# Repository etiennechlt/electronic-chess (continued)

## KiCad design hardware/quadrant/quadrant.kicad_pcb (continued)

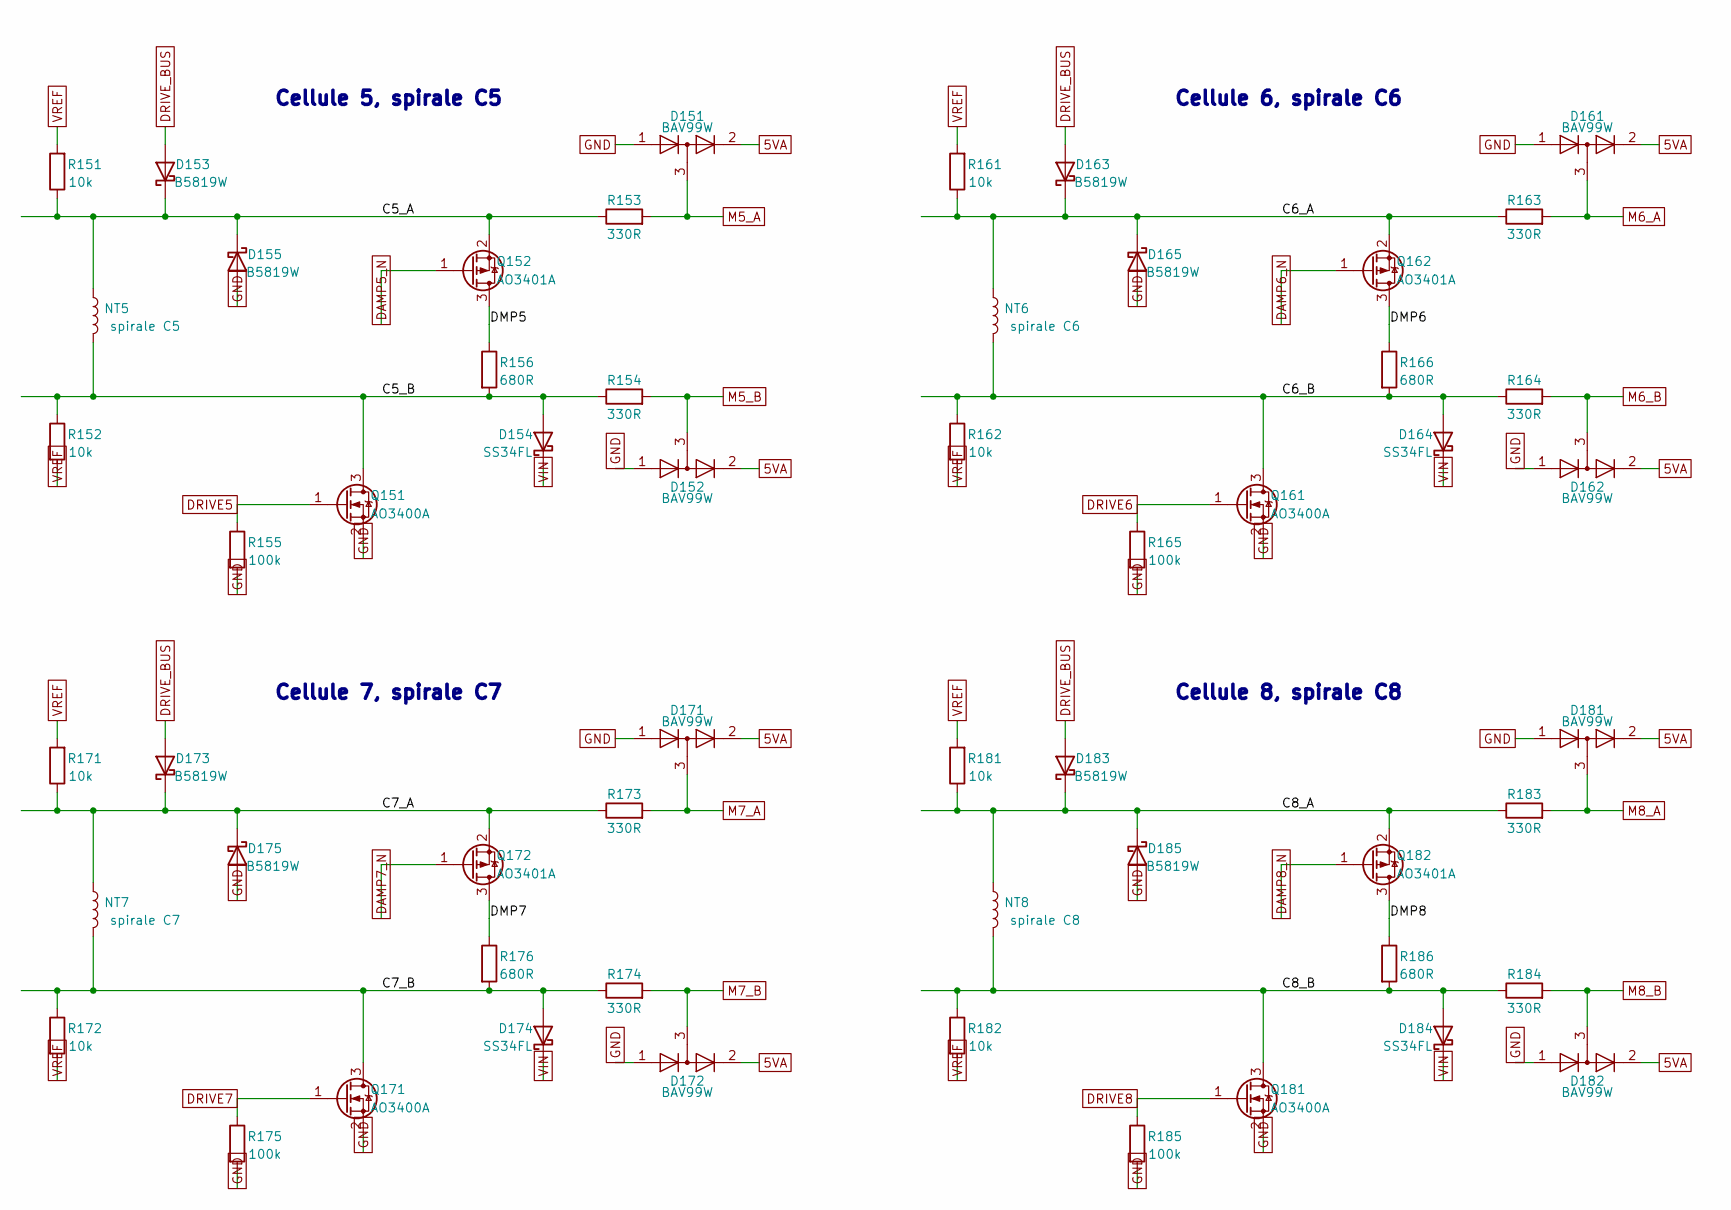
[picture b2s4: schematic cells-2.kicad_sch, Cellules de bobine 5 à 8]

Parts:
D151, D152, D161, D162, D171, D172, D181, D182: BAV99W; SOT-323_SC-70; MPN BAV99W
D153, D155, D163, D165, D173, D175, D183, D185: B5819W; D_SOD-123; MPN B5819W; LCSC C8598
D154, D164, D174, D184: SS34FL; D_SOD-123F; MPN SS34FL; LCSC C2480216
NT5: spirale C5; COIL_TIE
NT6: spirale C6; COIL_TIE
NT7: spirale C7; COIL_TIE
NT8: spirale C8; COIL_TIE
Q151, Q161, Q171, Q181: AO3400A; SOT-23; MPN AO3400A; LCSC C20917
Q152, Q162, Q172, Q182: AO3401A; SOT-23; MPN AO3401A; LCSC C15127
R151, R152, R161, R162, R171, R172, R181, R182: 10k; R_0603_1608Metric
R153, R154, R163, R164, R173, R174, R183, R184: 330R; R_0603_1608Metric
R155, R165, R175, R185: 100k; R_0402_1005Metric
R156, R166, R176, R186: 680R; R_0805_2012Metric

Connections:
5VA: D151.2 (A), D152.2 (A), D161.2 (A), D162.2 (A), D171.2 (A), D172.2 (A), D181.2 (A), D182.2 (A); also elsewhere on the board
C5_A: D153.1 (K), D155.1 (K), NT5.1, Q152.2 (S), R151.1, R153.1
C5_B: D154.2 (A), NT5.2, Q151.3 (D), R152.1, R154.1, R156.2
C6_A: D163.1 (K), D165.1 (K), NT6.1, Q162.2 (S), R161.1, R163.1
C6_B: D164.2 (A), NT6.2, Q161.3 (D), R162.1, R164.1, R166.2
C7_A: D173.1 (K), D175.1 (K), NT7.1, Q172.2 (S), R171.1, R173.1
C7_B: D174.2 (A), NT7.2, Q171.3 (D), R172.1, R174.1, R176.2
C8_A: D183.1 (K), D185.1 (K), NT8.1, Q182.2 (S), R181.1, R183.1
C8_B: D184.2 (A), NT8.2, Q181.3 (D), R182.1, R184.1, R186.2
DAMP5_N: Q152.1 (G); also elsewhere on the board
DAMP6_N: Q162.1 (G); also elsewhere on the board
DAMP7_N: Q172.1 (G); also elsewhere on the board
DAMP8_N: Q182.1 (G); also elsewhere on the board
DMP5: Q152.3 (D), R156.1
DMP6: Q162.3 (D), R166.1
DMP7: Q172.3 (D), R176.1
DMP8: Q182.3 (D), R186.1
DRIVE5: Q151.1 (G), R155.1; also elsewhere on the board
DRIVE6: Q161.1 (G), R165.1; also elsewhere on the board
DRIVE7: Q171.1 (G), R175.1; also elsewhere on the board
DRIVE8: Q181.1 (G), R185.1; also elsewhere on the board
DRIVE_BUS: D153.2 (A), D163.2 (A), D173.2 (A), D183.2 (A); also elsewhere on the board
GND: D151.1 (K), D152.1 (K), D155.2 (A), D161.1 (K), D162.1 (K), D165.2 (A), D171.1 (K), D172.1 (K), D175.2 (A), D181.1 (K), D182.1 (K), D185.2 (A), Q151.2 (S), Q161.2 (S), Q171.2 (S), Q181.2 (S), R155.2, R165.2, R175.2, R185.2; also elsewhere on the board
M5_A: D151.3 (K), R153.2; also elsewhere on the board
M5_B: D152.3 (K), R154.2; also elsewhere on the board
M6_A: D161.3 (K), R163.2; also elsewhere on the board
M6_B: D162.3 (K), R164.2; also elsewhere on the board
M7_A: D171.3 (K), R173.2; also elsewhere on the board
M7_B: D172.3 (K), R174.2; also elsewhere on the board
M8_A: D181.3 (K), R183.2; also elsewhere on the board
M8_B: D182.3 (K), R184.2; also elsewhere on the board
VIN: D154.1 (K), D164.1 (K), D174.1 (K), D184.1 (K); also elsewhere on the board
VREF: R151.2, R152.2, R161.2, R162.2, R171.2, R172.2, R181.2, R182.2; also elsewhere on the board

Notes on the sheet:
Cellule 5, spirale C5
Cellule 6, spirale C6
Cellule 7, spirale C7
Cellule 8, spirale C8

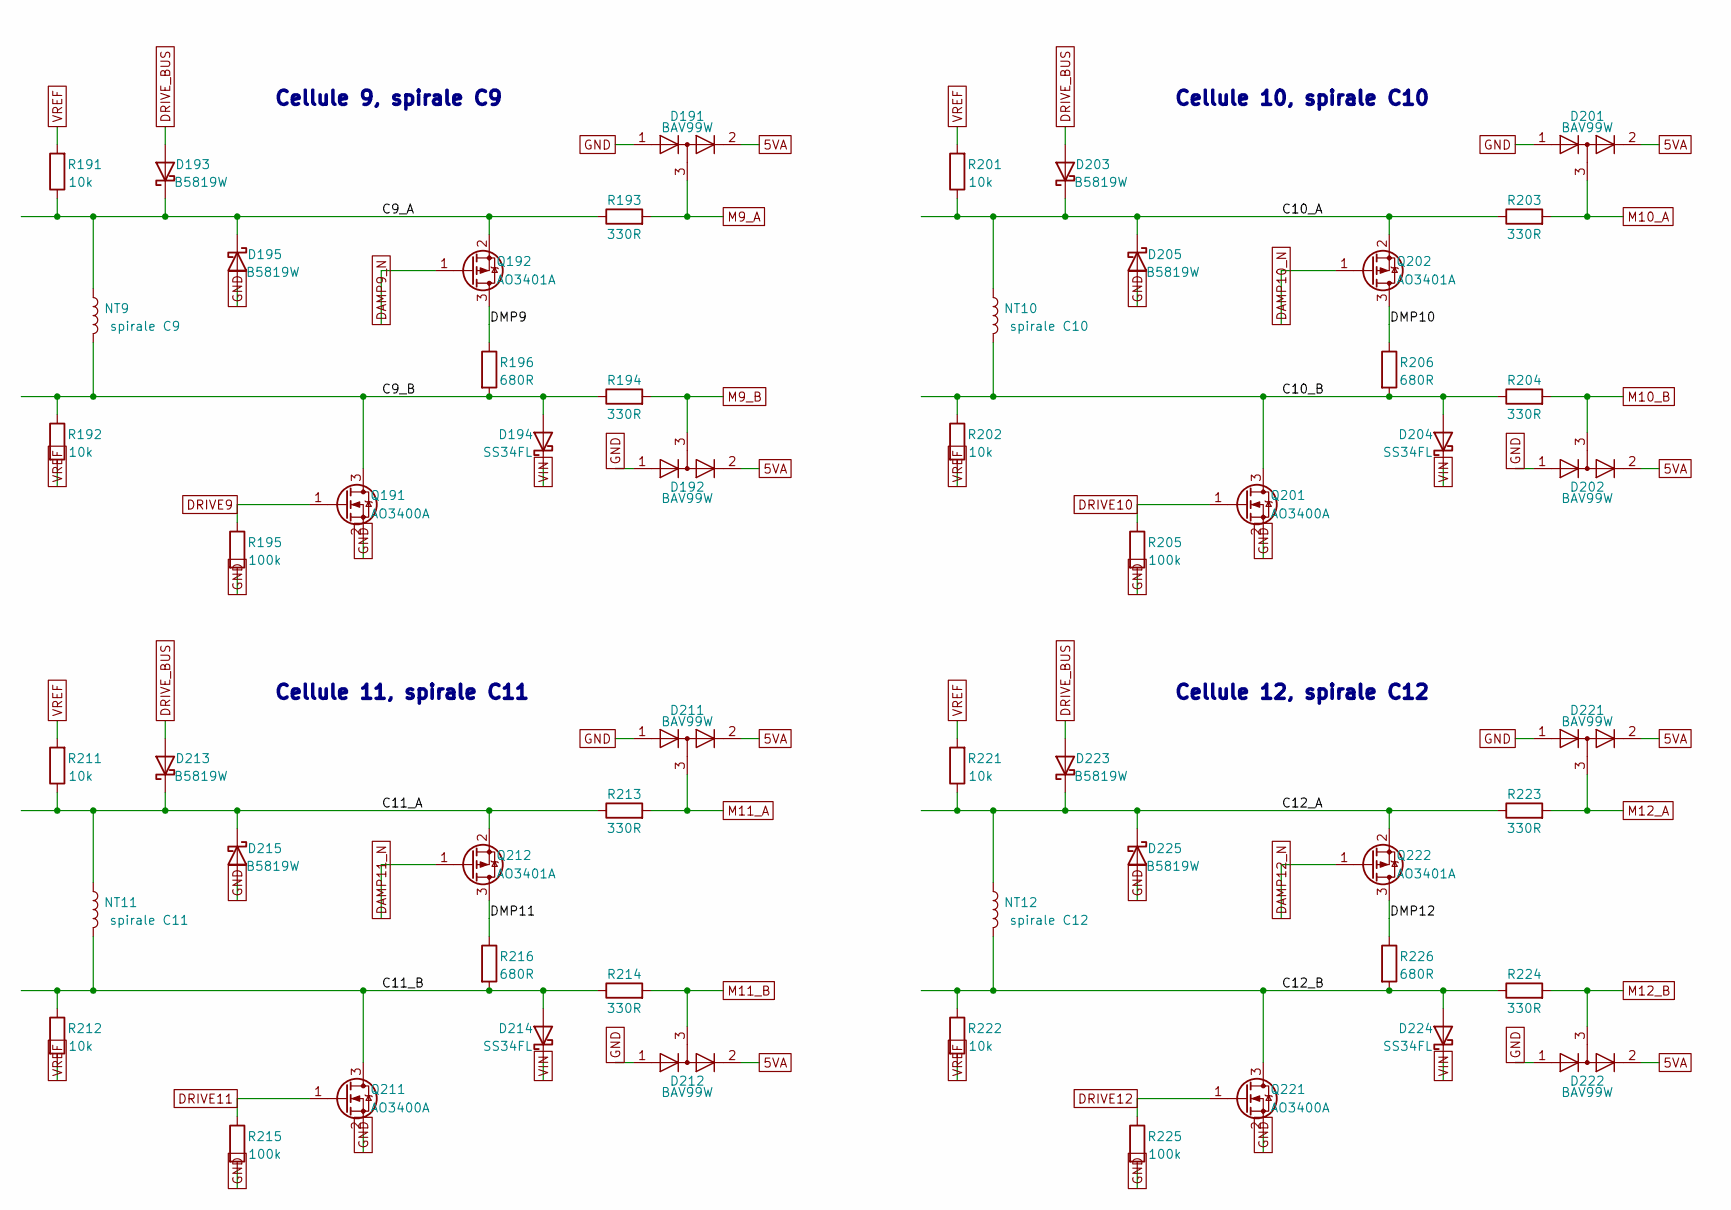
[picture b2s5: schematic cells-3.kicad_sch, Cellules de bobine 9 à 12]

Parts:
D191, D192, D201, D202, D211, D212, D221, D222: BAV99W; SOT-323_SC-70; MPN BAV99W
D193, D195, D203, D205, D213, D215, D223, D225: B5819W; D_SOD-123; MPN B5819W; LCSC C8598
D194, D204, D214, D224: SS34FL; D_SOD-123F; MPN SS34FL; LCSC C2480216
NT9: spirale C9; COIL_TIE
NT10: spirale C10; COIL_TIE
NT11: spirale C11; COIL_TIE
NT12: spirale C12; COIL_TIE
Q191, Q201, Q211, Q221: AO3400A; SOT-23; MPN AO3400A; LCSC C20917
Q192, Q202, Q212, Q222: AO3401A; SOT-23; MPN AO3401A; LCSC C15127
R191, R192, R201, R202, R211, R212, R221, R222: 10k; R_0603_1608Metric
R193, R194, R203, R204, R213, R214, R223, R224: 330R; R_0603_1608Metric
R195, R205, R215, R225: 100k; R_0402_1005Metric
R196, R206, R216, R226: 680R; R_0805_2012Metric

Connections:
5VA: D191.2 (A), D192.2 (A), D201.2 (A), D202.2 (A), D211.2 (A), D212.2 (A), D221.2 (A), D222.2 (A); also elsewhere on the board
C9_A: D193.1 (K), D195.1 (K), NT9.1, Q192.2 (S), R191.1, R193.1
C9_B: D194.2 (A), NT9.2, Q191.3 (D), R192.1, R194.1, R196.2
C10_A: D203.1 (K), D205.1 (K), NT10.1, Q202.2 (S), R201.1, R203.1
C10_B: D204.2 (A), NT10.2, Q201.3 (D), R202.1, R204.1, R206.2
C11_A: D213.1 (K), D215.1 (K), NT11.1, Q212.2 (S), R211.1, R213.1
C11_B: D214.2 (A), NT11.2, Q211.3 (D), R212.1, R214.1, R216.2
C12_A: D223.1 (K), D225.1 (K), NT12.1, Q222.2 (S), R221.1, R223.1
C12_B: D224.2 (A), NT12.2, Q221.3 (D), R222.1, R224.1, R226.2
DAMP9_N: Q192.1 (G); also elsewhere on the board
DAMP10_N: Q202.1 (G); also elsewhere on the board
DAMP11_N: Q212.1 (G); also elsewhere on the board
DAMP12_N: Q222.1 (G); also elsewhere on the board
DMP9: Q192.3 (D), R196.1
DMP10: Q202.3 (D), R206.1
DMP11: Q212.3 (D), R216.1
DMP12: Q222.3 (D), R226.1
DRIVE9: Q191.1 (G), R195.1; also elsewhere on the board
DRIVE10: Q201.1 (G), R205.1; also elsewhere on the board
DRIVE11: Q211.1 (G), R215.1; also elsewhere on the board
DRIVE12: Q221.1 (G), R225.1; also elsewhere on the board
DRIVE_BUS: D193.2 (A), D203.2 (A), D213.2 (A), D223.2 (A); also elsewhere on the board
GND: D191.1 (K), D192.1 (K), D195.2 (A), D201.1 (K), D202.1 (K), D205.2 (A), D211.1 (K), D212.1 (K), D215.2 (A), D221.1 (K), D222.1 (K), D225.2 (A), Q191.2 (S), Q201.2 (S), Q211.2 (S), Q221.2 (S), R195.2, R205.2, R215.2, R225.2; also elsewhere on the board
M9_A: D191.3 (K), R193.2; also elsewhere on the board
M9_B: D192.3 (K), R194.2; also elsewhere on the board
M10_A: D201.3 (K), R203.2; also elsewhere on the board
M10_B: D202.3 (K), R204.2; also elsewhere on the board
M11_A: D211.3 (K), R213.2; also elsewhere on the board
M11_B: D212.3 (K), R214.2; also elsewhere on the board
M12_A: D221.3 (K), R223.2; also elsewhere on the board
M12_B: D222.3 (K), R224.2; also elsewhere on the board
VIN: D194.1 (K), D204.1 (K), D214.1 (K), D224.1 (K); also elsewhere on the board
VREF: R191.2, R192.2, R201.2, R202.2, R211.2, R212.2, R221.2, R222.2; also elsewhere on the board

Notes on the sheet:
Cellule 9, spirale C9
Cellule 10, spirale C10
Cellule 11, spirale C11
Cellule 12, spirale C12

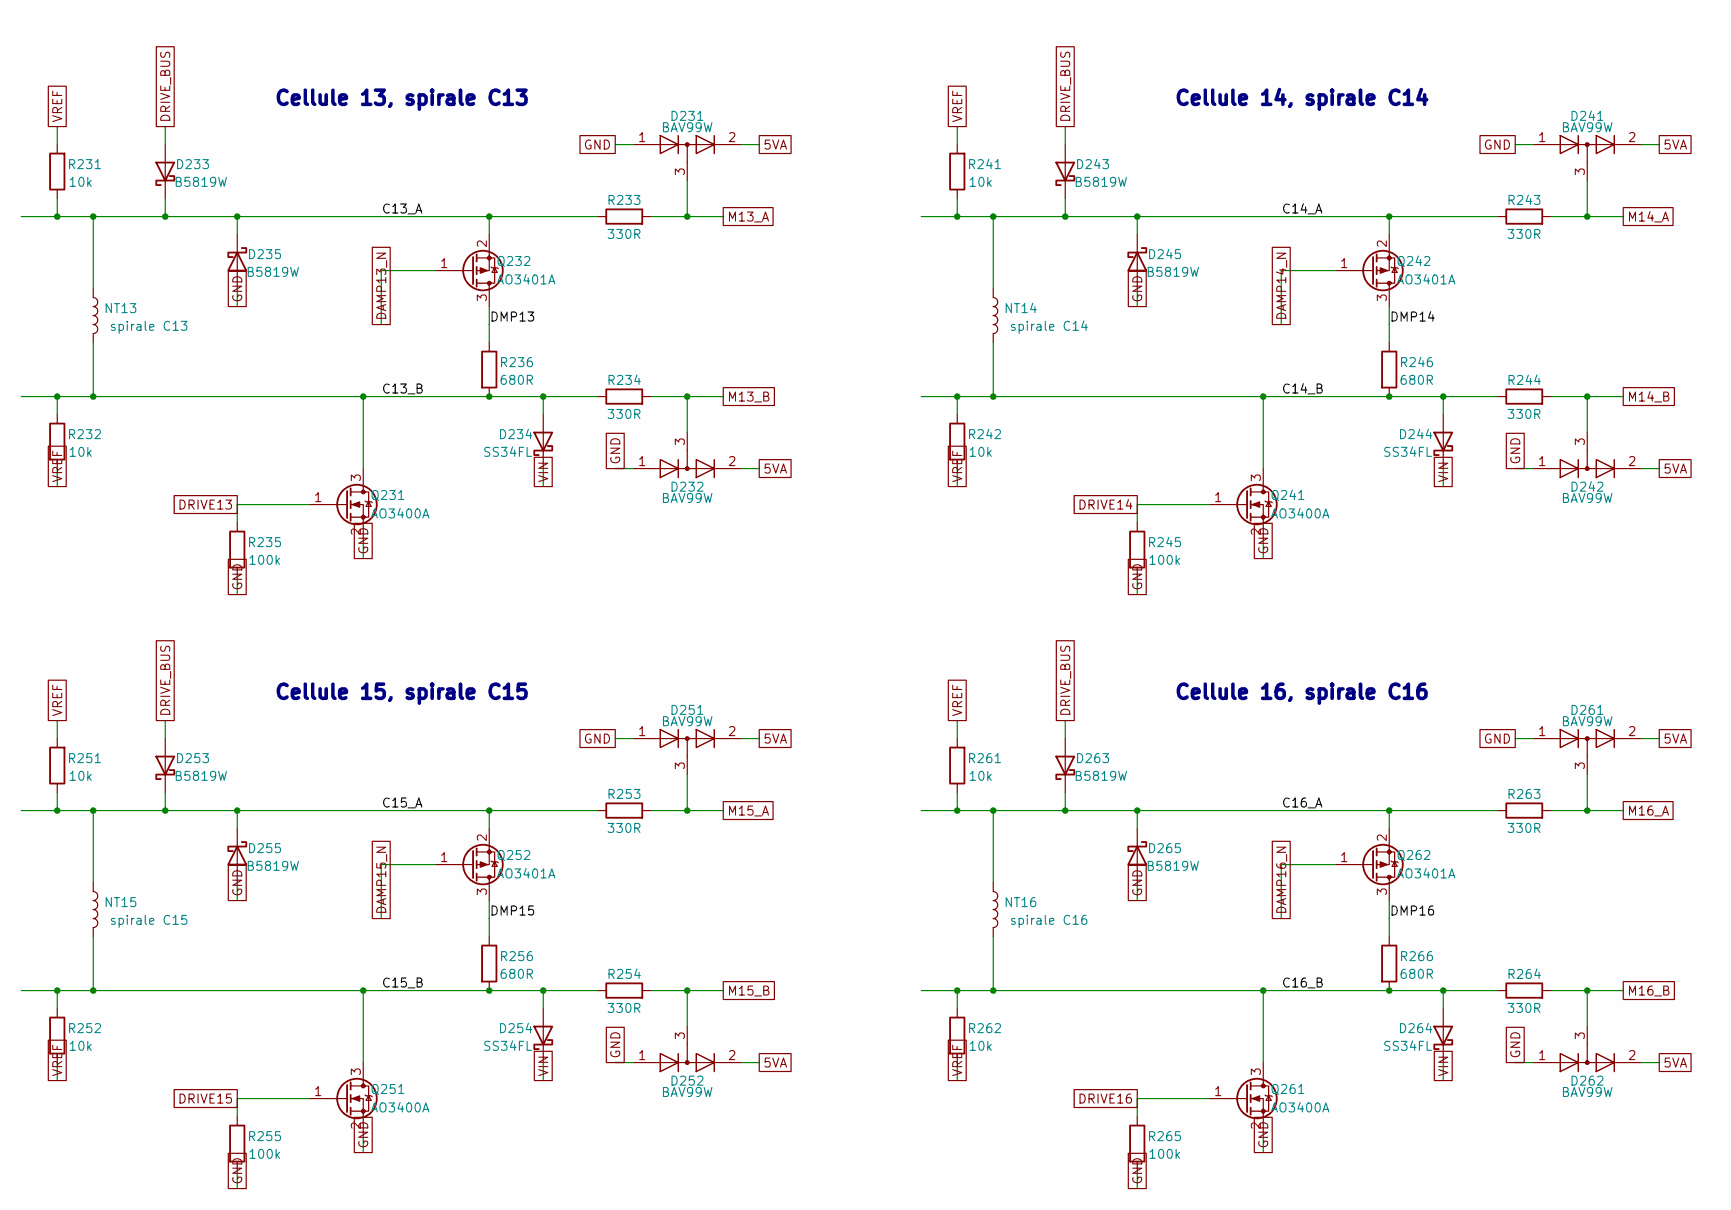
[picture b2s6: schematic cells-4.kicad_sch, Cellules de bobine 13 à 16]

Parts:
D231, D232, D241, D242, D251, D252, D261, D262: BAV99W; SOT-323_SC-70; MPN BAV99W
D233, D235, D243, D245, D253, D255, D263, D265: B5819W; D_SOD-123; MPN B5819W; LCSC C8598
D234, D244, D254, D264: SS34FL; D_SOD-123F; MPN SS34FL; LCSC C2480216
NT13: spirale C13; COIL_TIE
NT14: spirale C14; COIL_TIE
NT15: spirale C15; COIL_TIE
NT16: spirale C16; COIL_TIE
Q231, Q241, Q251, Q261: AO3400A; SOT-23; MPN AO3400A; LCSC C20917
Q232, Q242, Q252, Q262: AO3401A; SOT-23; MPN AO3401A; LCSC C15127
R231, R232, R241, R242, R251, R252, R261, R262: 10k; R_0603_1608Metric
R233, R234, R243, R244, R253, R254, R263, R264: 330R; R_0603_1608Metric
R235, R245, R255, R265: 100k; R_0402_1005Metric
R236, R246, R256, R266: 680R; R_0805_2012Metric

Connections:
5VA: D231.2 (A), D232.2 (A), D241.2 (A), D242.2 (A), D251.2 (A), D252.2 (A), D261.2 (A), D262.2 (A); also elsewhere on the board
C13_A: D233.1 (K), D235.1 (K), NT13.1, Q232.2 (S), R231.1, R233.1
C13_B: D234.2 (A), NT13.2, Q231.3 (D), R232.1, R234.1, R236.2
C14_A: D243.1 (K), D245.1 (K), NT14.1, Q242.2 (S), R241.1, R243.1
C14_B: D244.2 (A), NT14.2, Q241.3 (D), R242.1, R244.1, R246.2
C15_A: D253.1 (K), D255.1 (K), NT15.1, Q252.2 (S), R251.1, R253.1
C15_B: D254.2 (A), NT15.2, Q251.3 (D), R252.1, R254.1, R256.2
C16_A: D263.1 (K), D265.1 (K), NT16.1, Q262.2 (S), R261.1, R263.1
C16_B: D264.2 (A), NT16.2, Q261.3 (D), R262.1, R264.1, R266.2
DAMP13_N: Q232.1 (G); also elsewhere on the board
DAMP14_N: Q242.1 (G); also elsewhere on the board
DAMP15_N: Q252.1 (G); also elsewhere on the board
DAMP16_N: Q262.1 (G); also elsewhere on the board
DMP13: Q232.3 (D), R236.1
DMP14: Q242.3 (D), R246.1
DMP15: Q252.3 (D), R256.1
DMP16: Q262.3 (D), R266.1
DRIVE13: Q231.1 (G), R235.1; also elsewhere on the board
DRIVE14: Q241.1 (G), R245.1; also elsewhere on the board
DRIVE15: Q251.1 (G), R255.1; also elsewhere on the board
DRIVE16: Q261.1 (G), R265.1; also elsewhere on the board
DRIVE_BUS: D233.2 (A), D243.2 (A), D253.2 (A), D263.2 (A); also elsewhere on the board
GND: D231.1 (K), D232.1 (K), D235.2 (A), D241.1 (K), D242.1 (K), D245.2 (A), D251.1 (K), D252.1 (K), D255.2 (A), D261.1 (K), D262.1 (K), D265.2 (A), Q231.2 (S), Q241.2 (S), Q251.2 (S), Q261.2 (S), R235.2, R245.2, R255.2, R265.2; also elsewhere on the board
M13_A: D231.3 (K), R233.2; also elsewhere on the board
M13_B: D232.3 (K), R234.2; also elsewhere on the board
M14_A: D241.3 (K), R243.2; also elsewhere on the board
M14_B: D242.3 (K), R244.2; also elsewhere on the board
M15_A: D251.3 (K), R253.2; also elsewhere on the board
M15_B: D252.3 (K), R254.2; also elsewhere on the board
M16_A: D261.3 (K), R263.2; also elsewhere on the board
M16_B: D262.3 (K), R264.2; also elsewhere on the board
VIN: D234.1 (K), D244.1 (K), D254.1 (K), D264.1 (K); also elsewhere on the board
VREF: R231.2, R232.2, R241.2, R242.2, R251.2, R252.2, R261.2, R262.2; also elsewhere on the board

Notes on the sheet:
Cellule 13, spirale C13
Cellule 14, spirale C14
Cellule 15, spirale C15
Cellule 16, spirale C16

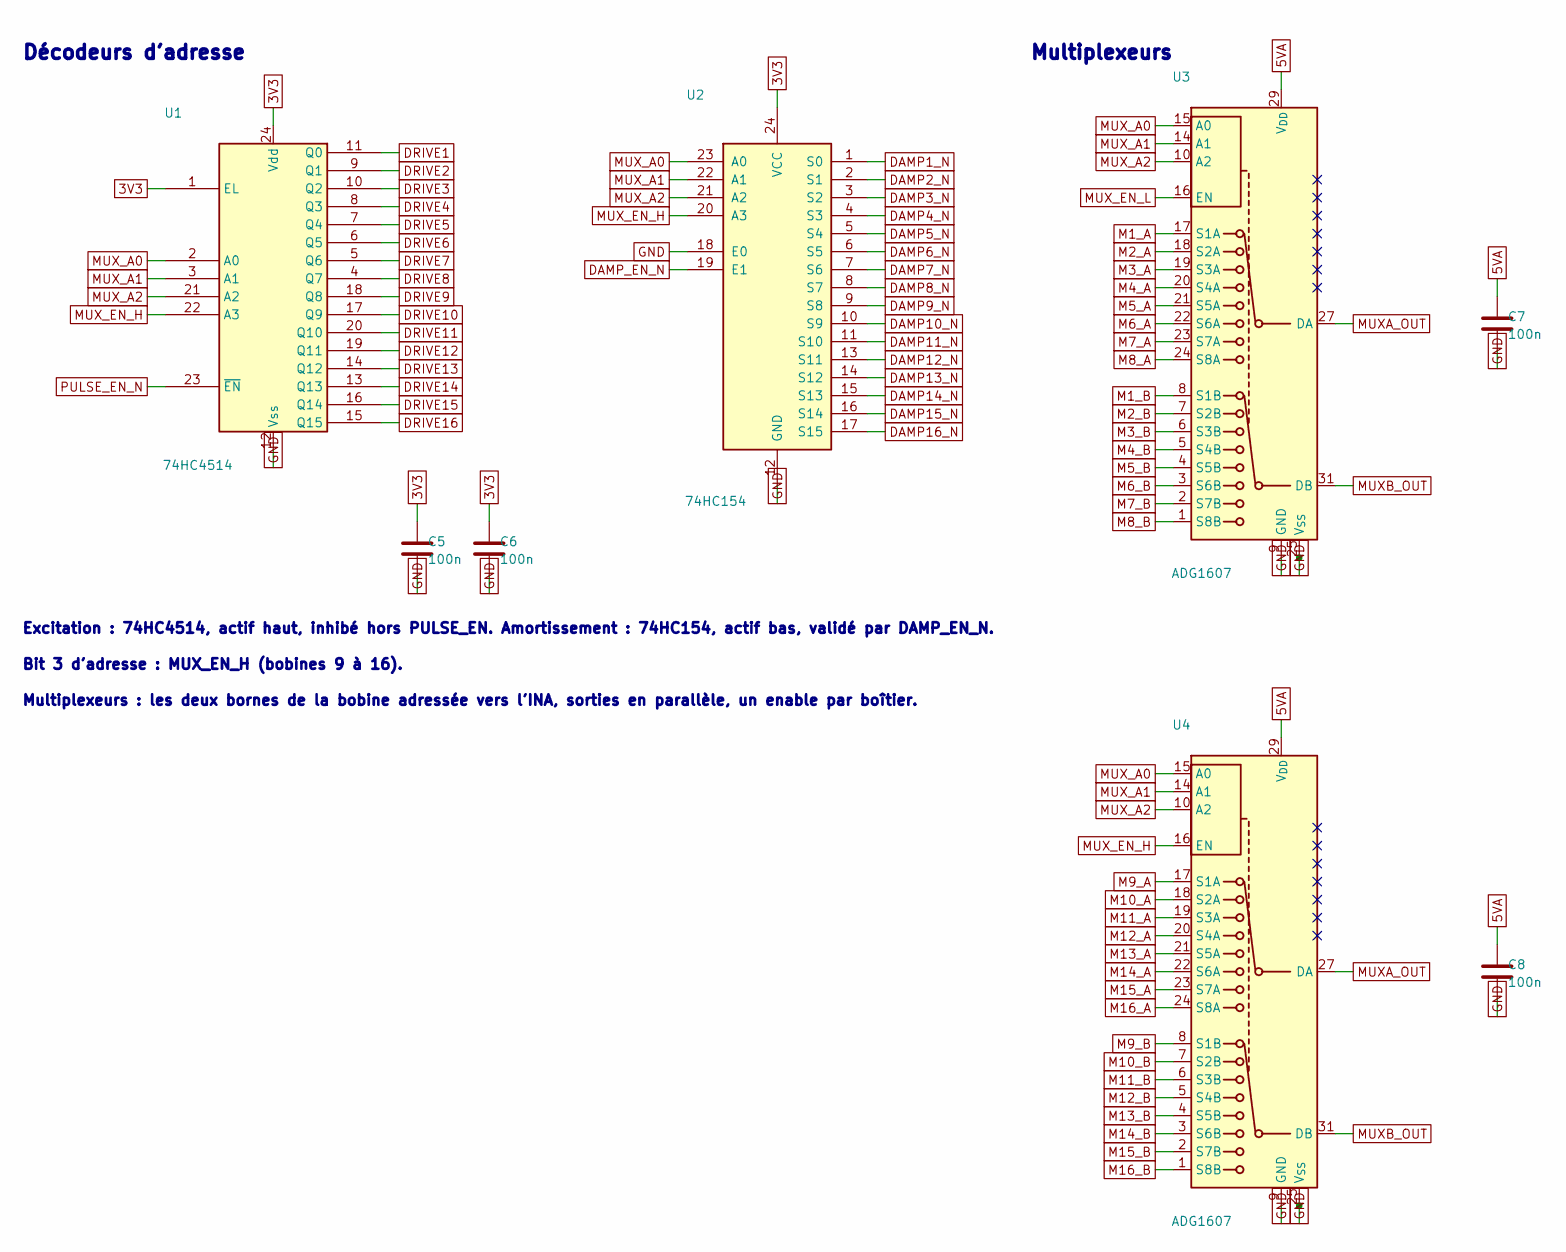
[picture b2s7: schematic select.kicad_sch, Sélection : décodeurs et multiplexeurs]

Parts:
C5, C6, C7, C8: 100n; C_0603_1608Metric
U1: 74HC4514; TSSOP-24_4.4x7.8mm_P0.65mm; MPN 74HC4514PW; LCSC C5615
U2: 74HC154; TSSOP-24_4.4x7.8mm_P0.65mm; MPN 74HC154PW; LCSC C5613
U3, U4: ADG1607; LFCSP-32-1EP_5x5mm_P0.5mm_EP3.1x3.1mm; MPN ADG1607BCPZ

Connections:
3V3: C5.1, C6.1, U1.1 (EL), U1.24 (Vdd), U2.24 (VCC); also elsewhere on the board
5VA: C7.1, C8.1, U3.29 (V_{DD}), U4.29 (V_{DD}); also elsewhere on the board
DAMP1_N: U2.1 (S0); also elsewhere on the board
DAMP2_N: U2.2 (S1); also elsewhere on the board
DAMP3_N: U2.3 (S2); also elsewhere on the board
DAMP4_N: U2.4 (S3); also elsewhere on the board
DAMP5_N: U2.5 (S4); also elsewhere on the board
DAMP6_N: U2.6 (S5); also elsewhere on the board
DAMP7_N: U2.7 (S6); also elsewhere on the board
DAMP8_N: U2.8 (S7); also elsewhere on the board
DAMP9_N: U2.9 (S8); also elsewhere on the board
DAMP10_N: U2.10 (S9); also elsewhere on the board
DAMP11_N: U2.11 (S10); also elsewhere on the board
DAMP12_N: U2.13 (S11); also elsewhere on the board
DAMP13_N: U2.14 (S12); also elsewhere on the board
DAMP14_N: U2.15 (S13); also elsewhere on the board
DAMP15_N: U2.16 (S14); also elsewhere on the board
DAMP16_N: U2.17 (S15); also elsewhere on the board
DAMP_EN_N: U2.19 (E1); also elsewhere on the board
DRIVE1: U1.11 (Q0); also elsewhere on the board
DRIVE2: U1.9 (Q1); also elsewhere on the board
DRIVE3: U1.10 (Q2); also elsewhere on the board
DRIVE4: U1.8 (Q3); also elsewhere on the board
DRIVE5: U1.7 (Q4); also elsewhere on the board
DRIVE6: U1.6 (Q5); also elsewhere on the board
DRIVE7: U1.5 (Q6); also elsewhere on the board
DRIVE8: U1.4 (Q7); also elsewhere on the board
DRIVE9: U1.18 (Q8); also elsewhere on the board
DRIVE10: U1.17 (Q9); also elsewhere on the board
DRIVE11: U1.20 (Q10); also elsewhere on the board
DRIVE12: U1.19 (Q11); also elsewhere on the board
DRIVE13: U1.14 (Q12); also elsewhere on the board
DRIVE14: U1.13 (Q13); also elsewhere on the board
DRIVE15: U1.16 (Q14); also elsewhere on the board
DRIVE16: U1.15 (Q15); also elsewhere on the board
GND: C5.2, C6.2, C7.2, C8.2, U1.12 (Vss), U2.12 (GND), U2.18 (E0), U3.9 (GND), U3.25 (V_{SS}), U3.33 (V_{SS}), U4.9 (GND), U4.25 (V_{SS}), U4.33 (V_{SS}); also elsewhere on the board
M1_A: U3.17 (S1A); also elsewhere on the board
M1_B: U3.8 (S1B); also elsewhere on the board
M2_A: U3.18 (S2A); also elsewhere on the board
M2_B: U3.7 (S2B); also elsewhere on the board
M3_A: U3.19 (S3A); also elsewhere on the board
M3_B: U3.6 (S3B); also elsewhere on the board
M4_A: U3.20 (S4A); also elsewhere on the board
M4_B: U3.5 (S4B); also elsewhere on the board
M5_A: U3.21 (S5A); also elsewhere on the board
M5_B: U3.4 (S5B); also elsewhere on the board
M6_A: U3.22 (S6A); also elsewhere on the board
M6_B: U3.3 (S6B); also elsewhere on the board
M7_A: U3.23 (S7A); also elsewhere on the board
M7_B: U3.2 (S7B); also elsewhere on the board
M8_A: U3.24 (S8A); also elsewhere on the board
M8_B: U3.1 (S8B); also elsewhere on the board
M9_A: U4.17 (S1A); also elsewhere on the board
M9_B: U4.8 (S1B); also elsewhere on the board
M10_A: U4.18 (S2A); also elsewhere on the board
M10_B: U4.7 (S2B); also elsewhere on the board
M11_A: U4.19 (S3A); also elsewhere on the board
M11_B: U4.6 (S3B); also elsewhere on the board
M12_A: U4.20 (S4A); also elsewhere on the board
M12_B: U4.5 (S4B); also elsewhere on the board
M13_A: U4.21 (S5A); also elsewhere on the board
M13_B: U4.4 (S5B); also elsewhere on the board
M14_A: U4.22 (S6A); also elsewhere on the board
M14_B: U4.3 (S6B); also elsewhere on the board
M15_A: U4.23 (S7A); also elsewhere on the board
M15_B: U4.2 (S7B); also elsewhere on the board
M16_A: U4.24 (S8A); also elsewhere on the board
M16_B: U4.1 (S8B); also elsewhere on the board
MUXA_OUT: U3.27 (DA), U4.27 (DA); also elsewhere on the board
MUXB_OUT: U3.31 (DB), U4.31 (DB); also elsewhere on the board
MUX_A0: U1.2 (A0), U2.23 (A0), U3.15 (A0), U4.15 (A0); also elsewhere on the board
MUX_A1: U1.3 (A1), U2.22 (A1), U3.14 (A1), U4.14 (A1); also elsewhere on the board
MUX_A2: U1.21 (A2), U2.21 (A2), U3.10 (A2), U4.10 (A2); also elsewhere on the board
MUX_EN_H: U1.22 (A3), U2.20 (A3), U4.16 (EN); also elsewhere on the board
MUX_EN_L: U3.16 (EN); also elsewhere on the board
PULSE_EN_N: U1.23 (~EN); also elsewhere on the board

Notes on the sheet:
Décodeurs d'adresse
Excitation : 74HC4514, actif haut, inhibé hors PULSE_EN. Amortissement : 74HC154, actif bas, validé par DAMP_EN_N.
Bit 3 d'adresse : MUX_EN_H (bobines 9 à 16).
Multiplexeurs
Multiplexeurs : les deux bornes de la bobine adressée vers l'INA, sorties en parallèle, un enable par boîtier.

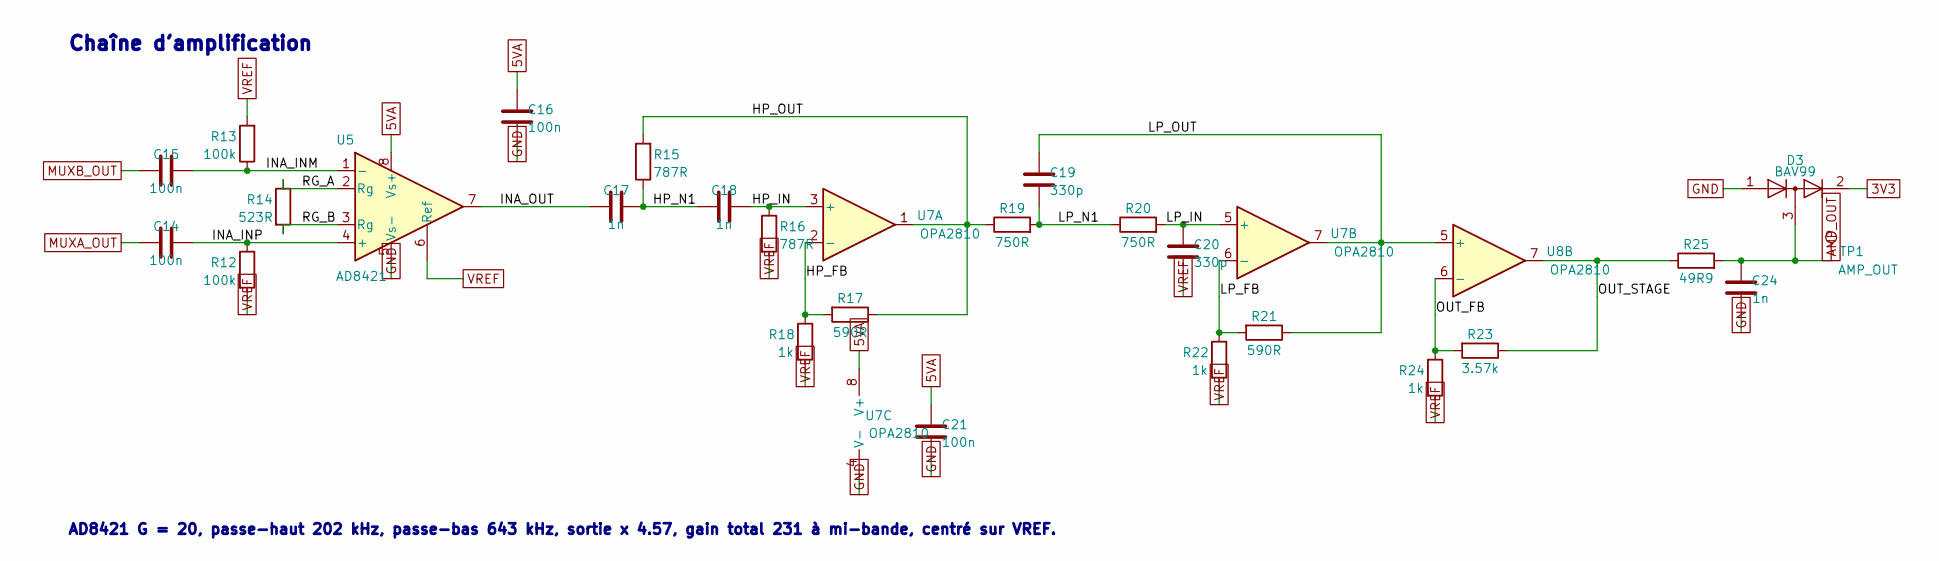
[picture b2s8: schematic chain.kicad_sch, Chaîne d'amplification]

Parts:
C14, C15, C16, C21: 100n; C_0603_1608Metric
C17, C18, C24: 1n; C_0603_1608Metric
C19, C20: 330p; C_0603_1608Metric
D3: BAV99; SOT-23; MPN BAV99; LCSC C2500
R12, R13: 100k; R_0603_1608Metric
R14: 523R; R_0603_1608Metric
R15, R16: 787R; R_0603_1608Metric
R17, R21: 590R; R_0603_1608Metric
R18, R22, R24: 1k; R_0603_1608Metric
R19, R20: 750R; R_0603_1608Metric
R23: 3.57k; R_0603_1608Metric
R25: 49R9; R_0603_1608Metric
TP1: AMP_OUT; TestPoint_Pad_1.5x1.5mm
U5: AD8421; SOIC-8_3.9x4.9mm_P1.27mm; MPN AD8421ARZ; LCSC C462186
U7, U8: OPA2810; SOIC-8_3.9x4.9mm_P1.27mm; MPN OPA2810IDR; LCSC C2059830

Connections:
3V3: D3.2 (A); also elsewhere on the board
5VA: C16.1, C21.1, U5.8 (Vs+), U7.8 (V+); also elsewhere on the board
AMP_OUT: C24.1, D3.3 (K), R25.2, TP1.1; also elsewhere on the board
GND: C16.2, C21.2, C24.2, D3.1 (K), U5.5 (Vs-), U7.4 (V-); also elsewhere on the board
HP_FB: R17.2, R18.1, U7.2 (-)
HP_IN: C18.2, R16.1, U7.3 (+)
HP_N1: C17.2, C18.1, R15.1
HP_OUT: R15.2, R17.1, R19.1, U7.1
INA_INM: C15.2, R13.1, U5.1 (-)
INA_INP: C14.2, R12.1, U5.4 (+)
INA_OUT: C17.1, U5.7
LP_FB: R21.2, R22.1, U7.6 (-)
LP_IN: C20.1, R20.2, U7.5 (+)
LP_N1: C19.1, R19.2, R20.1
LP_OUT: C19.2, R21.1, U7.7, U8.5 (+)
MUXA_OUT: C14.1; also elsewhere on the board
MUXB_OUT: C15.1; also elsewhere on the board
OUT_FB: R23.2, R24.1, U8.6 (-)
OUT_STAGE: R23.1, R25.1, U8.7
RG_A: R14.1, U5.2 (Rg)
RG_B: R14.2, U5.3 (Rg)
VREF: C20.2, R12.2, R13.2, R16.2, R18.2, R22.2, R24.2, U5.6 (Ref); also elsewhere on the board

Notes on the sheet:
Chaîne d'amplification
AD8421 G = 20, passe-haut 202 kHz, passe-bas 643 kHz, sortie x 4.57, gain total 231 à mi-bande, centré sur VREF.

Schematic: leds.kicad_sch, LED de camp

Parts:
CL1, CL2, CL3, CL4, CL5, CL6, CL7, CL8, CL9, CL10, CL11, CL12, CL13, CL14, CL15, CL16, CL17, CL18, CL19, CL20, CL21, CL22, CL23, CL24, CL25, CL26, CL27, CL28, CL29, CL30, CL31, CL32: 100n; C_0603_1608Metric
LD1, LD2, LD3, LD4, LD5, LD6, LD7, LD8, LD9, LD10, LD11, LD12, LD13, LD14, LD15, LD16, LD17, LD18, LD19, LD20, LD21, LD22, LD23, LD24, LD25, LD26, LD27, LD28, LD29, LD30, LD31, LD32: WS2812B; LED_WS2812B_PLCC4_5.0x5.0mm_P3.2mm; MPN WS2812B; LCSC C2761795

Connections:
5V_LED: CL1.1, CL2.1, CL3.1, CL4.1, CL5.1, CL6.1, CL7.1, CL8.1, CL9.1, CL10.1, CL11.1, CL12.1, CL13.1, CL14.1, CL15.1, CL16.1, CL17.1, CL18.1, CL19.1, CL20.1, CL21.1, CL22.1, CL23.1, CL24.1, CL25.1, CL26.1, CL27.1, CL28.1, CL29.1, CL30.1, CL31.1, CL32.1, LD1.1 (VDD), LD2.1 (VDD), LD3.1 (VDD), LD4.1 (VDD), LD5.1 (VDD), LD6.1 (VDD), LD7.1 (VDD), LD8.1 (VDD), LD9.1 (VDD), LD10.1 (VDD), LD11.1 (VDD), LD12.1 (VDD), LD13.1 (VDD), LD14.1 (VDD), LD15.1 (VDD), LD16.1 (VDD), LD17.1 (VDD), LD18.1 (VDD), LD19.1 (VDD), LD20.1 (VDD), LD21.1 (VDD), LD22.1 (VDD), LD23.1 (VDD), LD24.1 (VDD), LD25.1 (VDD), LD26.1 (VDD), LD27.1 (VDD), LD28.1 (VDD), LD29.1 (VDD), LD30.1 (VDD), LD31.1 (VDD), LD32.1 (VDD); also elsewhere on the board
GND: CL1.2, CL2.2, CL3.2, CL4.2, CL5.2, CL6.2, CL7.2, CL8.2, CL9.2, CL10.2, CL11.2, CL12.2, CL13.2, CL14.2, CL15.2, CL16.2, CL17.2, CL18.2, CL19.2, CL20.2, CL21.2, CL22.2, CL23.2, CL24.2, CL25.2, CL26.2, CL27.2, CL28.2, CL29.2, CL30.2, CL31.2, CL32.2, LD1.3 (VSS), LD2.3 (VSS), LD3.3 (VSS), LD4.3 (VSS), LD5.3 (VSS), LD6.3 (VSS), LD7.3 (VSS), LD8.3 (VSS), LD9.3 (VSS), LD10.3 (VSS), LD11.3 (VSS), LD12.3 (VSS), LD13.3 (VSS), LD14.3 (VSS), LD15.3 (VSS), LD16.3 (VSS), LD17.3 (VSS), LD18.3 (VSS), LD19.3 (VSS), LD20.3 (VSS), LD21.3 (VSS), LD22.3 (VSS), LD23.3 (VSS), LD24.3 (VSS), LD25.3 (VSS), LD26.3 (VSS), LD27.3 (VSS), LD28.3 (VSS), LD29.3 (VSS), LD30.3 (VSS), LD31.3 (VSS), LD32.3 (VSS); also elsewhere on the board
LED_DIN: LD1.4 (DIN); also elsewhere on the board
LED_DOUT: LD32.2 (DOUT); also elsewhere on the board
LED_L1: LD1.2 (DOUT), LD2.4 (DIN)
LED_L2: LD2.2 (DOUT), LD3.4 (DIN)
LED_L3: LD3.2 (DOUT), LD4.4 (DIN)
LED_L4: LD4.2 (DOUT), LD5.4 (DIN)
LED_L5: LD5.2 (DOUT), LD6.4 (DIN)
LED_L6: LD6.2 (DOUT), LD7.4 (DIN)
LED_L7: LD7.2 (DOUT), LD8.4 (DIN)
LED_L8: LD8.2 (DOUT), LD9.4 (DIN)
LED_L9: LD9.2 (DOUT), LD10.4 (DIN)
LED_L10: LD10.2 (DOUT), LD11.4 (DIN)
LED_L11: LD11.2 (DOUT), LD12.4 (DIN)
LED_L12: LD12.2 (DOUT), LD13.4 (DIN)
LED_L13: LD13.2 (DOUT), LD14.4 (DIN)
LED_L14: LD14.2 (DOUT), LD15.4 (DIN)
LED_L15: LD15.2 (DOUT), LD16.4 (DIN)
LED_L16: LD16.2 (DOUT), LD17.4 (DIN)
LED_L17: LD17.2 (DOUT), LD18.4 (DIN)
LED_L18: LD18.2 (DOUT), LD19.4 (DIN)
LED_L19: LD19.2 (DOUT), LD20.4 (DIN)
LED_L20: LD20.2 (DOUT), LD21.4 (DIN)
LED_L21: LD21.2 (DOUT), LD22.4 (DIN)
LED_L22: LD22.2 (DOUT), LD23.4 (DIN)
LED_L23: LD23.2 (DOUT), LD24.4 (DIN)
LED_L24: LD24.2 (DOUT), LD25.4 (DIN)
LED_L25: LD25.2 (DOUT), LD26.4 (DIN)
LED_L26: LD26.2 (DOUT), LD27.4 (DIN)
LED_L27: LD27.2 (DOUT), LD28.4 (DIN)
LED_L28: LD28.2 (DOUT), LD29.4 (DIN)
LED_L29: LD29.2 (DOUT), LD30.4 (DIN)
LED_L30: LD30.2 (DOUT), LD31.4 (DIN)
LED_L31: LD31.2 (DOUT), LD32.4 (DIN)

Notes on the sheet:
LED de camp
WS2812B, deux par case, chaînées dans l'ordre du serpentin des rangées.

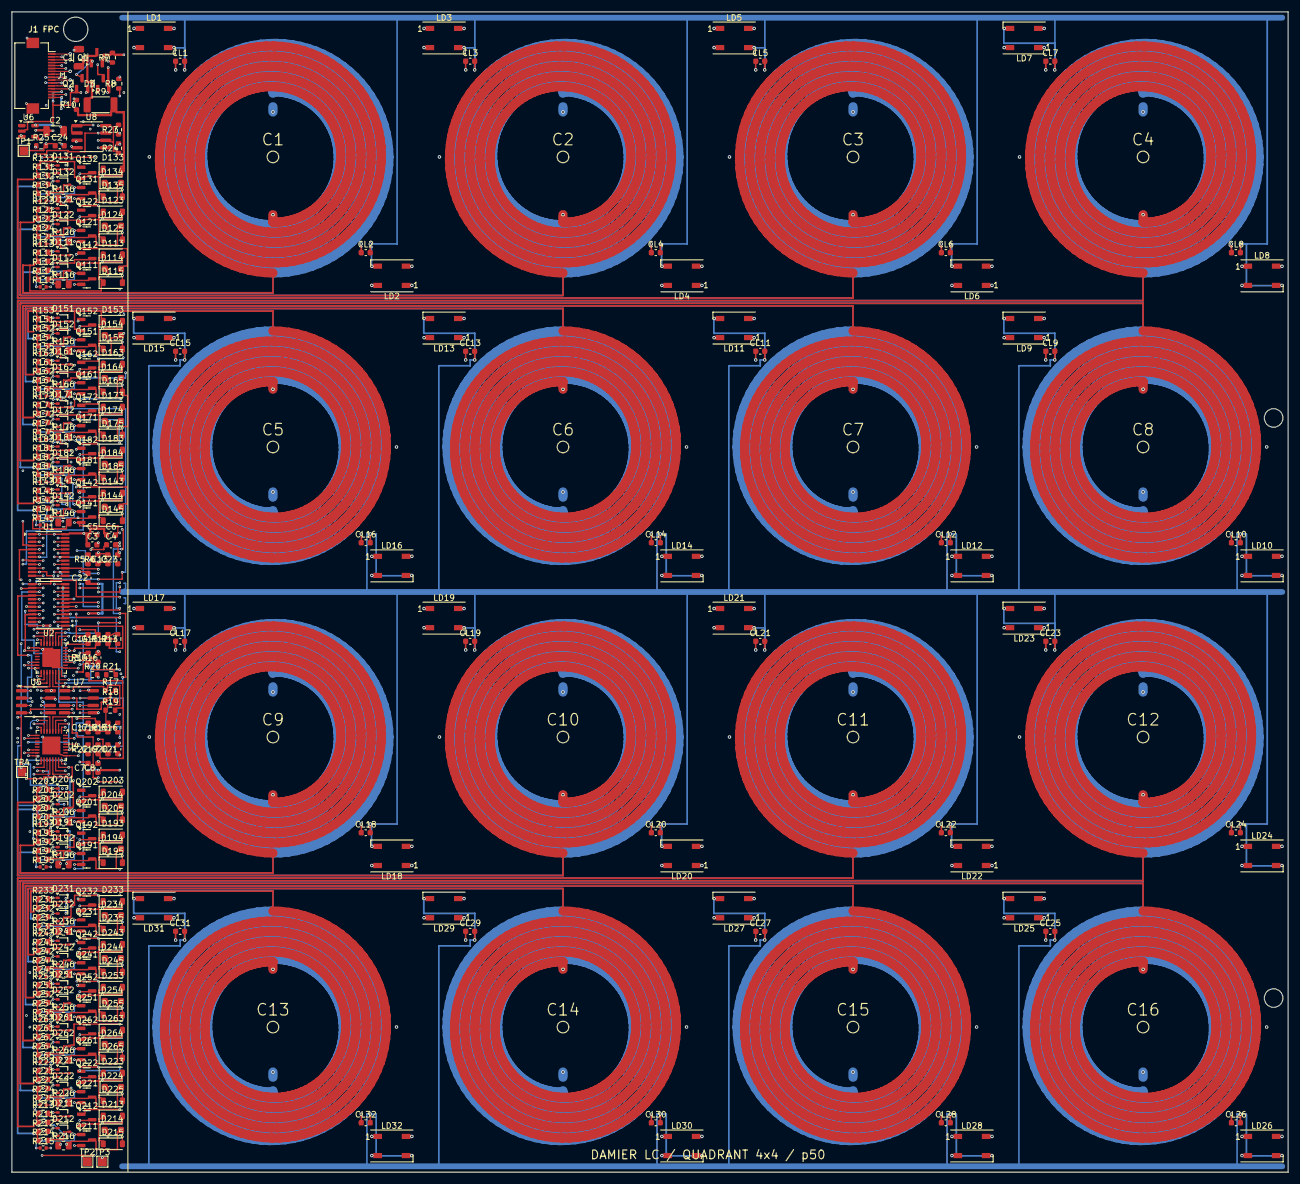
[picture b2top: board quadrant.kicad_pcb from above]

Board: 4 copper layers, 220.0 x 200.0 mm, 347 parts (0 on the bottom side), 181 nets.

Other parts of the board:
H1, H2: NPTH; NPTH_3.2
P1: NPTH; NPTH_4.2
